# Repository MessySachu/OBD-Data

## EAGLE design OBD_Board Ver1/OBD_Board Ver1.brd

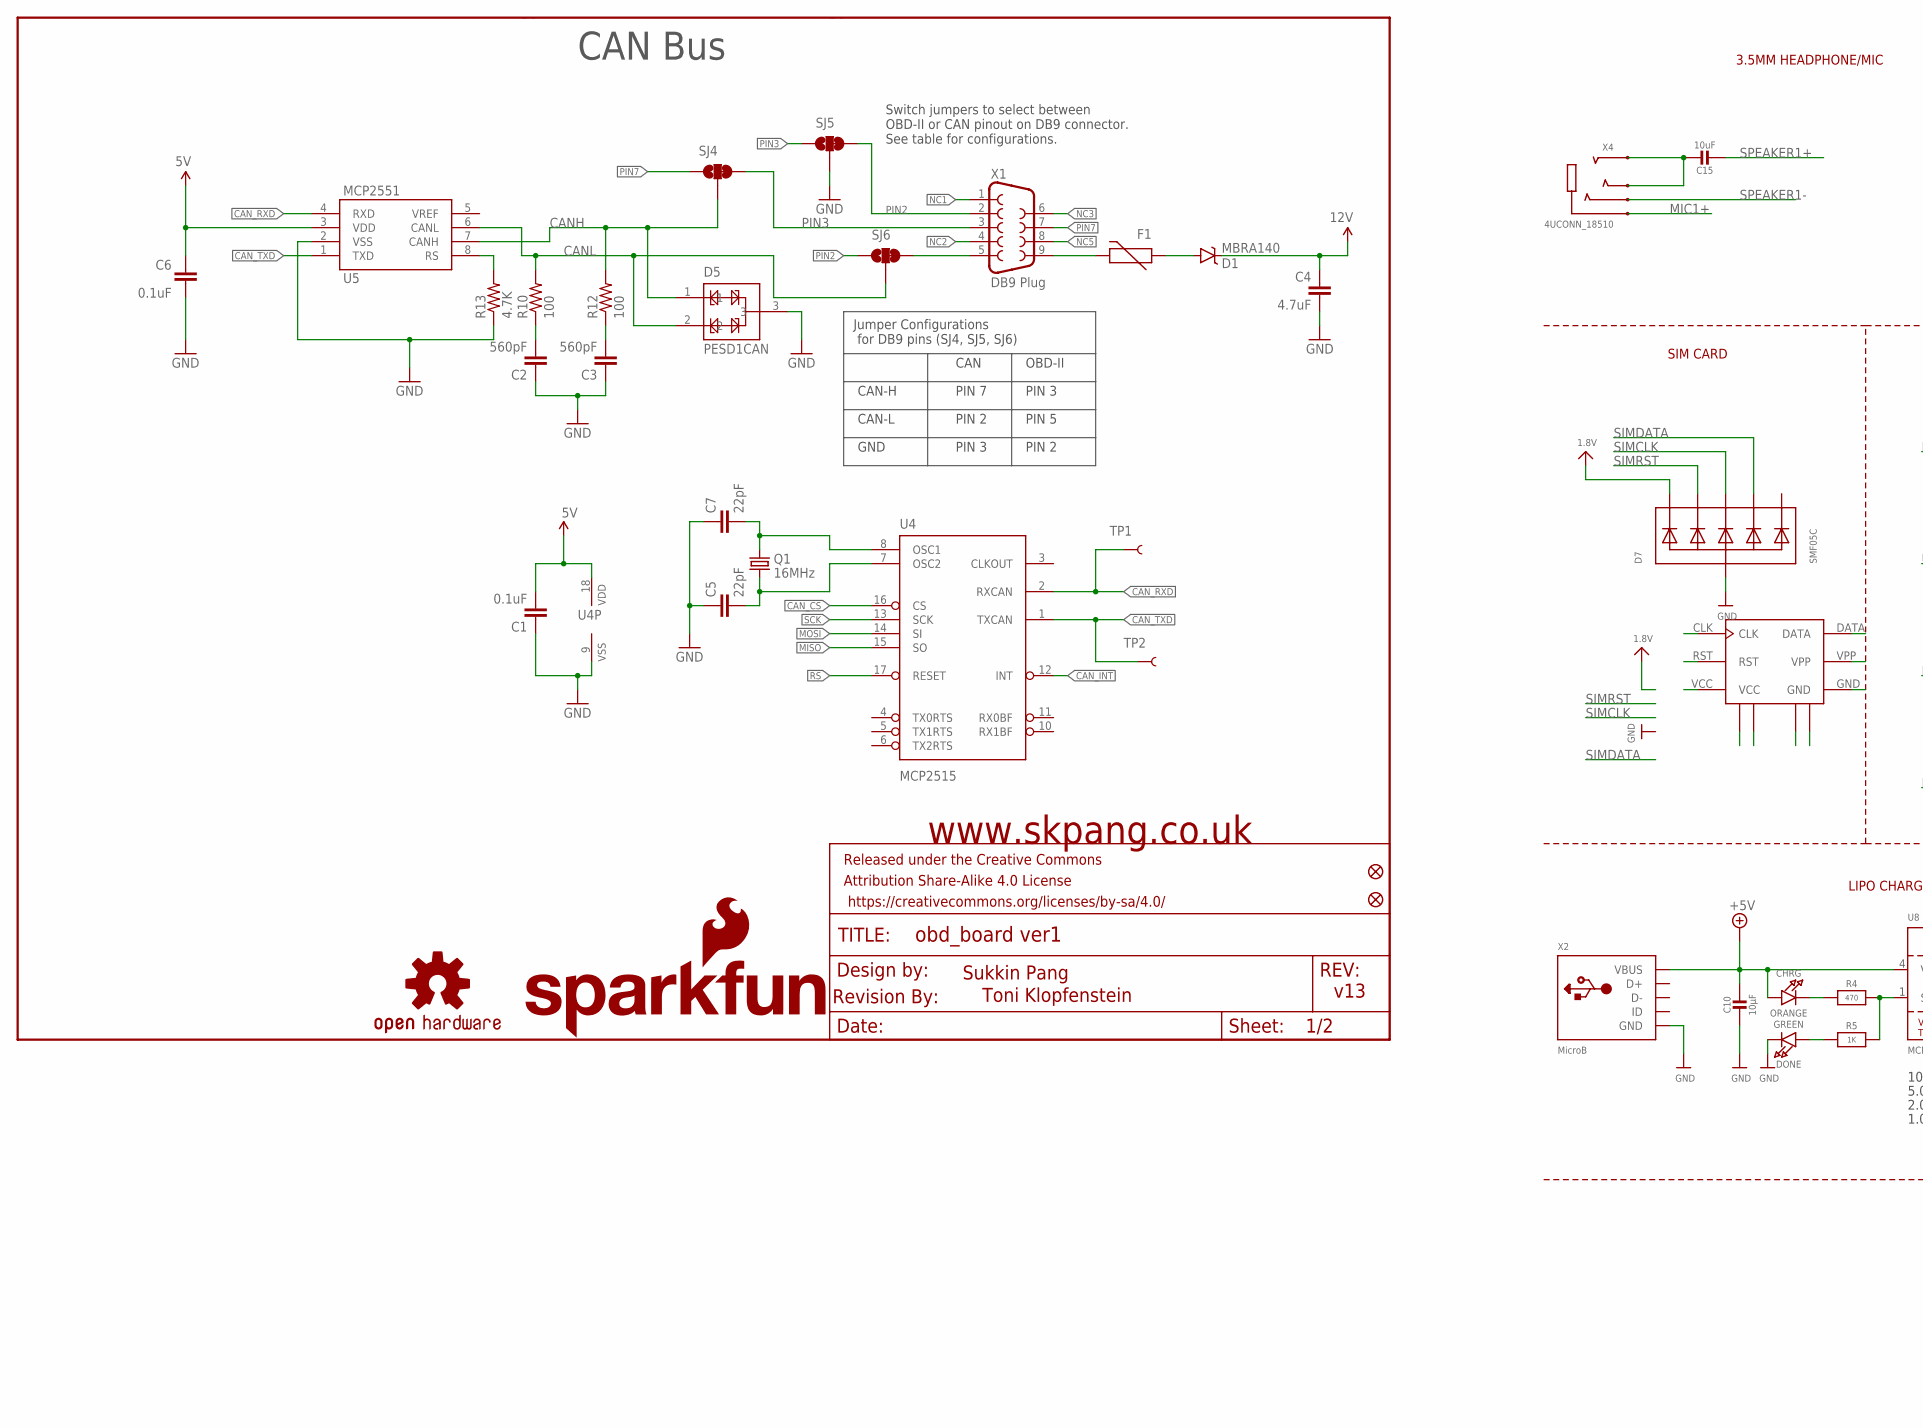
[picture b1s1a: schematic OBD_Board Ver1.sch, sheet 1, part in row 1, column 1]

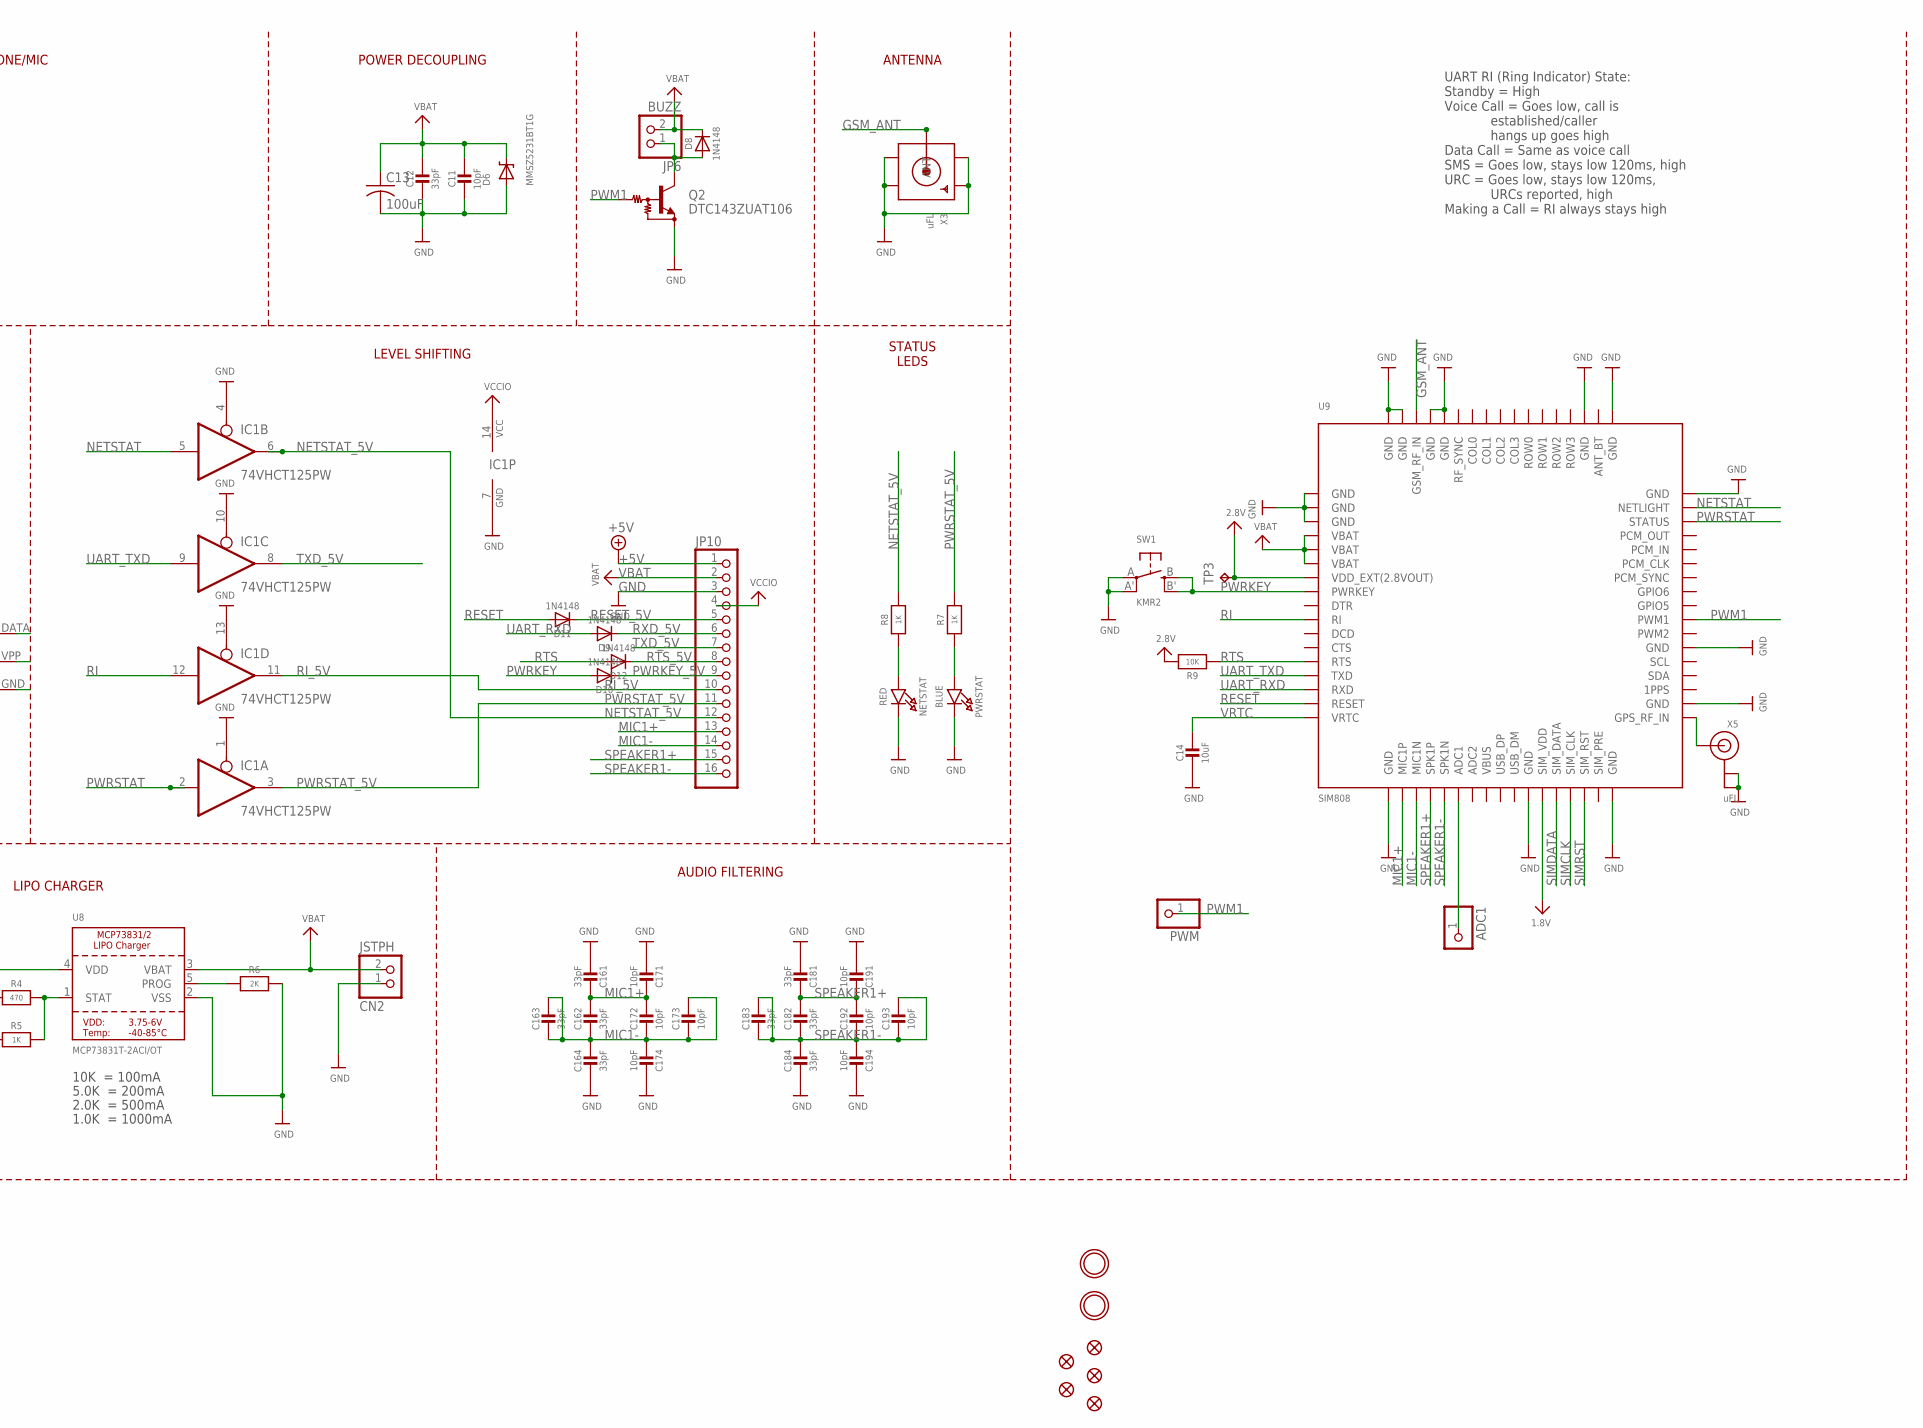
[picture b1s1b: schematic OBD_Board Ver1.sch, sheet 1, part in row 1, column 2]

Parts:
ADC1: PINHD-1X1CB; 1X01-CLEANBIG
C1, C6: 0.1uF; 0603-CAP
C2, C3: 560pF; 0603-CAP
C4: 4.7uF; 0603-CAP
C5, C7: 22pF; 0603-CAP
C10: 10µF; 0805-NO
C11: 10pF; 0805-NO
C12: 33pF; 0805-NO
C13: 100uF; C1210
C14, C15: 10uF; 0805-NO
C16, C18: 33pF; RESPACK_4X0603
C17, C19: 10pF; RESPACK_4X0603
CHRG: ORANGE; CHIPLED_0805_NOOUTLINE
CN2: JSTPH; JSTPH2
D1: MBRA140; SMA-DIODE
D5: PESD1CAN; SOT23-3
D6: MMSZ5231BT1G; SOD-123
D7: SMF05C; SOT363
D8, D9, D10, D11, D12: 1N4148; SOD-323
DONE: GREEN; CHIPLED_0805_NOOUTLINE
F1: PTCTHERMISTOR1206; PTC-1206
FID1, FID2, FID3, FID4, FID5: FIDUCIAL""; FIDUCIAL_1MM
FRAME1: FRAME-LETTER; CREATIVE_COMMONS
IC1: 74VHCT125PW; TSSOP14
JP2, JP3: FIDUCIAL1X2; FIDUCIAL-1X2
JP4: SFE_LOGO_NAME_FLAME.1_INCH; SFE_LOGO_NAME_FLAME_.1
JP6: BUZZ; 1X02_ROUND
JP10: HEADER-1X16ROUND; 1X16_ROUND
LOGO1: OSHW-LOGOM; OSHW-LOGO-M
NETSTAT: RED; CHIPLED_0805_NOOUTLINE
PWM: PINHD-1X1CB; 1X01-CLEANBIG
PWRSTAT: BLUE; CHIPLED_0805_NOOUTLINE
Q1: 16MHz; CRYSTAL-SMD-5X3
Q2: DTC143ZUAT106; SC59-BEC
R4: 470; 0805-NO
R5, R7, R8: 1K; 0805-NO
R6: 2K; 0805-NO
R9: 10K; 0805-NO
R10, R12: 100; 0603-RES
R13: 4.7K; 0603-RES
SJ4, SJ5, SJ6: JUMPER-PAD-3-2OF3_NC_BY_TRACE_SMALL; PAD-JUMPER-3-2OF3_NC_BY_TRACE_YES_SILK_FULL_BOX
SW1: KMR2; BTN_KMR2_4.6X2.8
TP1, TP2: TEST-POINT3X5; PAD.03X.05
TP3: TPTP11R; TP11R
U4: MCP2515; SO-18W
U5: MCP2551; SO08
U8: MCP73831T-2ACI/OT; SOT23-5
U9: SIM808; SIM900_SMT
U$1: REVISION
U$25: SCU-W0822XR-06
U$33, U$34: MOUNTINGHOLE2.5; MOUNTINGHOLE_2.5_PLATED
X1: DB9 Plug; DB9_MALE
X2: MicroB; 4UCONN_20329
X3: uFL; SMA_EDGELAUNCH_UFL
X4: 4UCONN_18510
X5: uFL; U.FL

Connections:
1.8V: D7.1 (C1), U9.P$29 (SIM_VDD), U$25.VCC
2.8V: R9.2, TP3.TP, U9.P$7 (VDD_EXT(2.8VOUT))
5V: C1.2, C6.2, U4.18 (VDD), U5.3 (VDD); also elsewhere on the board
12V: C4.1, D1.C; also elsewhere on the board
+5V: C10.1, CHRG.A, JP10.1, U8.4 (VDD), X2.VBUS
CANH: D5.1, R12.2, SJ4.2, U5.7 (CANH)
CANL: D5.2, R10.2, SJ6.2, U5.6 (CANL)
CAN_CS: U4.16 (CS); also elsewhere on the board
CAN_INT: U4.12 (INT); also elsewhere on the board
CAN_RXD: TP1.P$1, U4.2 (RXCAN), U5.4 (RXD)
CAN_TXD: TP2.P$1, U4.1 (TXCAN), U5.1 (TXD)
GND: C1.1, C2.1, C3.1, C4.2, C5.1, C6.1, C7.1, C10.2, C11.2, C12.2, C13.2, C14.2, C16.5 (2), C16.8 (2), C17.4 (1), C17.8 (2), C18.5 (2), C18.8 (2), C19.4 (1), C19.8 (2), CN2.1, D5.3, D6.A, D7.2 (A), DONE.C, IC1.1 (OE), IC1.4 (OE), IC1.7 (GND), IC1.10 (OE), IC1.13 (OE), JP10.3, NETSTAT.C, PWRSTAT.C, Q2.E, R6.2, R13.1, SJ5.2, SW1.A, SW1.A' (P1), U4.9 (VSS), U5.2 (VSS), U8.2 (VSS), U9.P$1 (GND), U9.P$2 (GND), U9.P$3 (GND), U9.P$18 (GND), U9.P$28 (GND), U9.P$34 (GND), U9.P$36 (GND), U9.P$40 (GND), U9.P$51 (GND), U9.P$52 (GND), U9.P$54 (GND), U9.P$64 (GND), U9.P$65 (GND), U9.P$67 (GND), U9.P$68 (GND), U$25.GND, U$25.GND_1 (GND1), U$25.GND_2 (GND2), U$25.GND_3 (GND3), U$25.GND_4 (GND4), X2.BASE@1 (GND), X2.BASE@2 (GND), X2.GND, X2.SPRT@1 (GND), X2.SPRT@2 (GND), X2.SPRT@3 (GND), X2.SPRT@4 (GND), X3.GND@1 (GND1), X3.GND@2 (GND2), X3.GND@3 (GND3), X3.GND@4 (GND4), X5.1 (GND), X5.2 (GND); also elsewhere on the board
GSM_ANT: U9.P$66 (GSM_RF_IN), X3.P (ANT)
HP+: C15.1, X4.2-TIP (RING3), X4.3-OUTER_SLEEVE (RING2)
MIC1+: C16.1, C16.2 (1), C17.1, C17.2 (1), JP10.13, U9.P$19 (MIC1P), X4.1-GND (TIP)
MIC1-: C16.3 (1), C16.4 (1), C16.6 (2), C16.7 (2), C17.3 (1), C17.5 (2), C17.6 (2), C17.7 (2), JP10.14, U9.P$20 (MIC1N)
MISO: U4.15 (SO); also elsewhere on the board
MOSI: U4.14 (SI); also elsewhere on the board
unnamed: SJ6.3, X1.5
unnamed: CHRG.C, R4.1
unnamed: R4.2, R5.2, U8.1 (STAT)
unnamed: R6.1, U8.5 (PROG)
unnamed: C2.2, R10.1
unnamed: C3.2, R12.1
unnamed: DONE.A, R5.1
unnamed: PWRSTAT.A, R7.1
unnamed: F1.2, X1.9
unnamed: R13.2, U5.8 (RS)
unnamed: D1.A, F1.1
unnamed: C7.2, Q1.3 (2), U4.8 (OSC1)
unnamed: C5.2, Q1.1, U4.7 (OSC2)
unnamed: NETSTAT.A, R8.1
unnamed: D8.A, JP6.1, Q2.C
unnamed: U9.P$35 (GPS_RF_IN), X5.3 (SIGNAL)
unnamed: ADC1.1, U9.P$23 (ADC1)
NC1: X1.1
NC2: X1.4
NC3: X1.6
NC5: X1.8
NETSTAT: IC1.5 (I), U9.P$50 (NETLIGHT)
NETSTAT_5V: IC1.6 (O), JP10.12, R8.2
PIN2: SJ5.3, SJ6.1, X1.2
PIN3: SJ4.3, SJ5.1, X1.3
PIN7: SJ4.1, X1.7
PWM1: PWM.1, Q2.B, U9.P$42 (PWM1)
PWRKEY: D10.A, SW1.B (S), SW1.B' (S1), U9.P$8 (PWRKEY)
PWRKEY_5V: D10.C, JP10.9
PWRSTAT: IC1.2 (I), U9.P$49 (STATUS)
PWRSTAT_5V: IC1.3 (O), JP10.11, R7.2
RESET: D11.A, U9.P$16 (RESET)
RESET_5V: D11.C, JP10.5
RI: IC1.12 (I), U9.P$10 (RI)
RI_5V: IC1.11 (O), JP10.10
RS: U4.17 (RESET); also elsewhere on the board
RTS: D12.A, R9.1, U9.P$13 (RTS)
RTS_5V: D12.C, JP10.8
RXD_5V: D9.C, JP10.6
SCK: U4.13 (SCK); also elsewhere on the board
SIMCLK: D7.4 (C3), U9.P$31 (SIM_CLK), U$25.CLK
SIMDATA: D7.5 (C4), U9.P$30 (SIM_DATA), U$25.DATA
SIMRST: D7.3 (C2), U9.P$32 (SIM_RST), U$25.RST
SPEAKER1+: C15.2, C18.1, C18.2 (1), C19.1, C19.2 (1), JP10.15, U9.P$21 (SPK1P)
SPEAKER1-: C18.3 (1), C18.4 (1), C18.6 (2), C18.7 (2), C19.3 (1), C19.5 (2), C19.6 (2), C19.7 (2), JP10.16, U9.P$22 (SPK1N), X4.4-INNER_SLEEVE (RING1)
TXD_5V: IC1.8 (O), JP10.7
UART_RXD: D9.A, U9.P$15 (RXD)
UART_TXD: IC1.9 (I), U9.P$14 (TXD)
VBAT: C11.1, C12.1, C13.1, CN2.2, D6.C, D8.C, JP6.2, JP10.2, U8.3 (VBAT), U9.P$4 (VBAT), U9.P$5 (VBAT), U9.P$6 (VBAT)
VBUS: U9.P$25 (VBUS)
VCCIO: IC1.14 (VCC), JP10.4
VRTC: C14.1, U9.P$17 (VRTC)

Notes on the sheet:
www.skpang.co.uk
Toni Klopfenstein
CAN Bus
CAN
OBD-II
CAN-H
CAN-L
GND
PIN 5
PIN 2
PIN 3
PIN 7
Jumper Configurations for DB9 pins (SJ4, SJ5, SJ6)
Switch jumpers to select between OBD-II or CAN pinout on DB9 connector. See table for configurations.
v13
Sukkin Pang
10K = 100mA
5.0K = 200mA
2.0K = 500mA
1.0K = 1000mA
UART RI (Ring Indicator) State: Standby = High Voice Call = Goes low, call is established/caller hangs up goes high Data Call = Same as voice call SMS = Goes low, stays low 120ms, high URC = Goes low, stays low 120ms, URCs reported, high Making a Call = RI always stays high
ANTENNA
POWER DECOUPLING
3.5MM HEADPHONE/MIC
SIM CARD
LEVEL SHIFTING
LIPO CHARGER
AUDIO FILTERING
STATUS LEDS

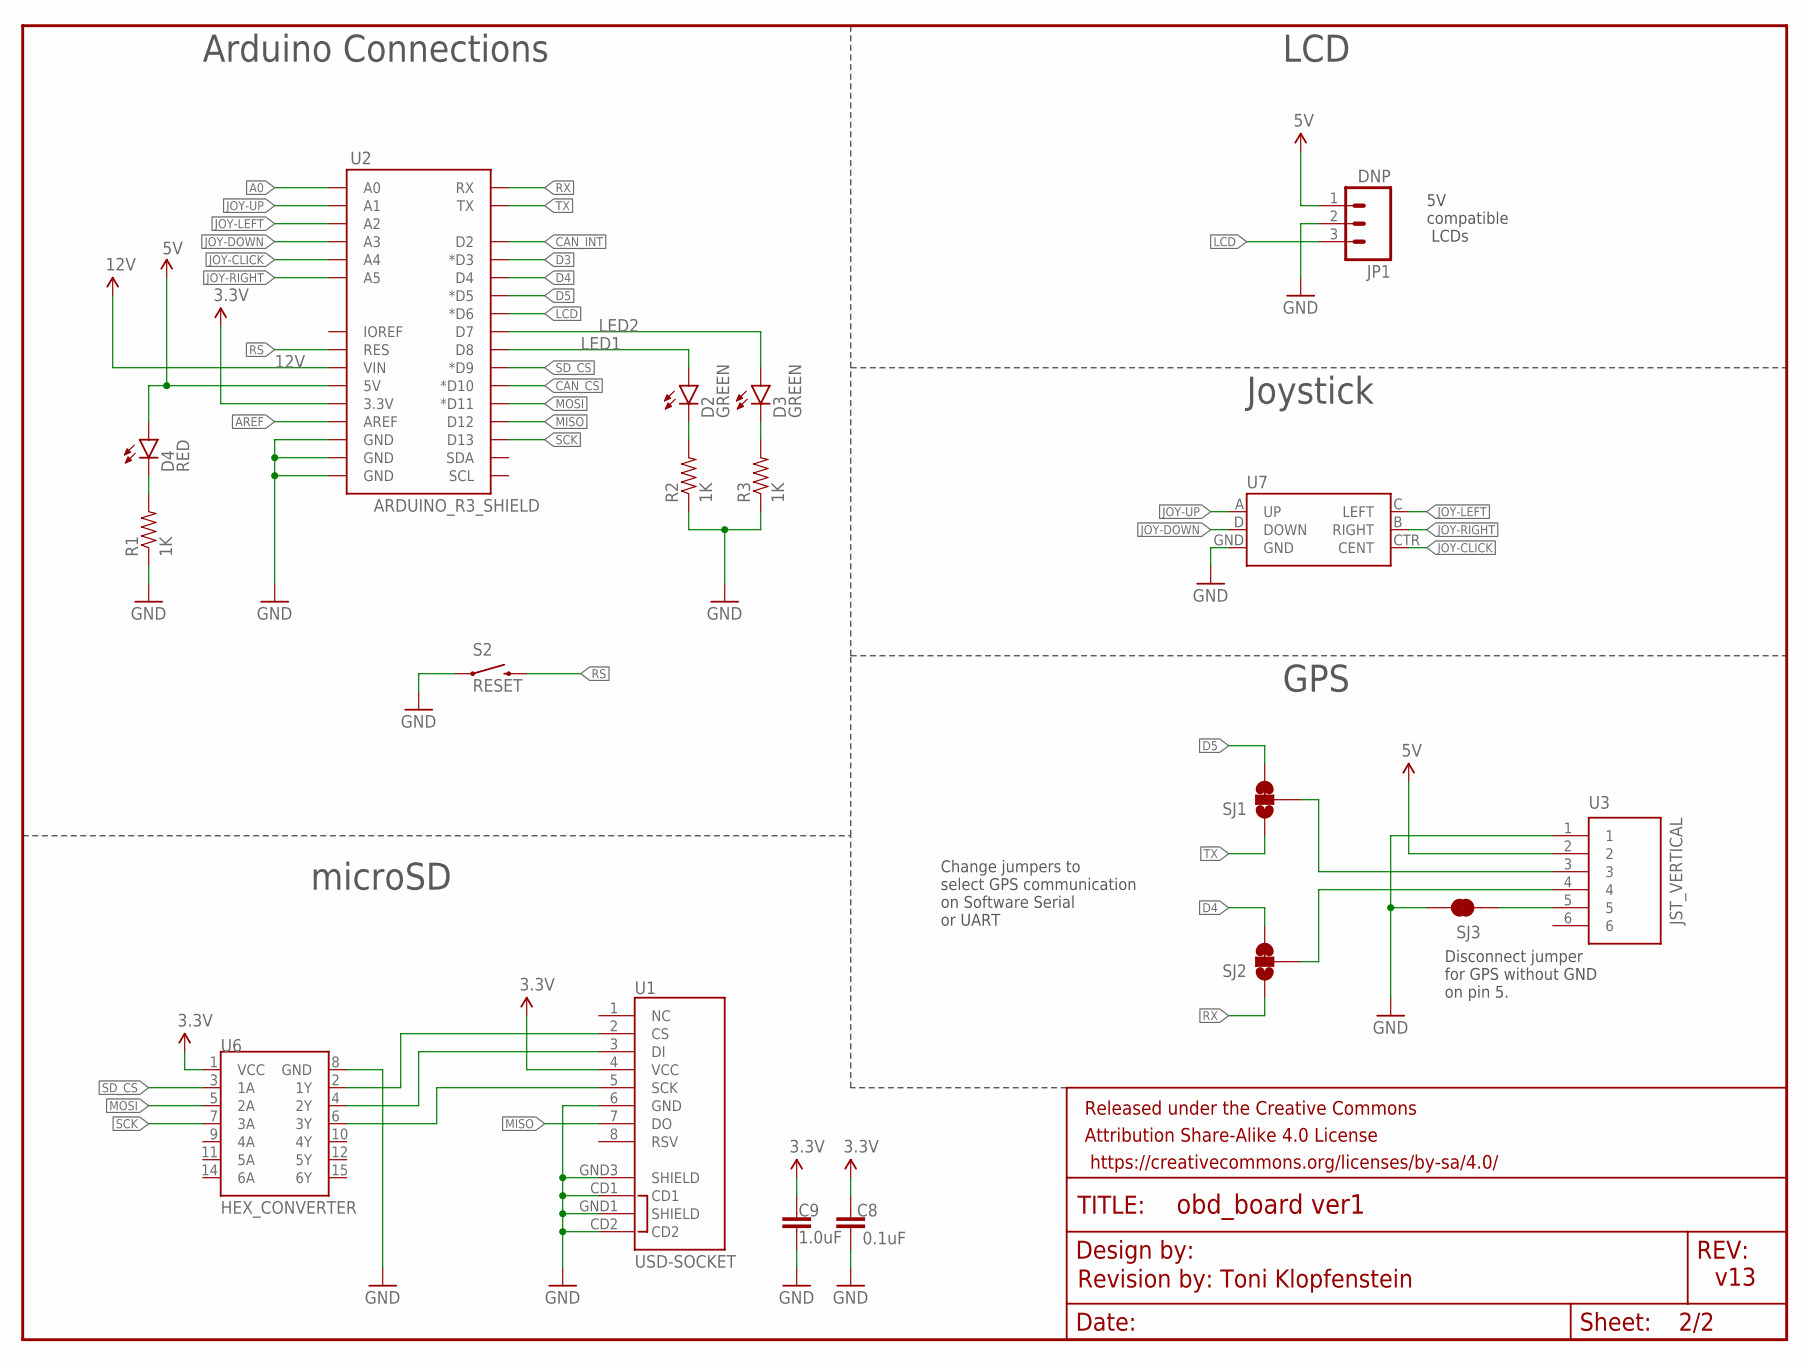
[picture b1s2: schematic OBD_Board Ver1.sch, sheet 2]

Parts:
C8: 0.1uF; 0603-CAP
C9: 1.0uF; 0603-CAP
D2, D3: GREEN; LED-0603
D4: RED; LED-0603
FRAME2: FRAME-LETTERNO_PACKAGE; DUMMY
JP1: DNP; MOLEX-1X3_LOCK
R1, R2, R3: 1K; 0603-RES
S2: RESET; TACTILE-SWITCH-SMD
SJ1, SJ2: JUMPER-PAD-3-2OF3_NC_BY_TRACE_SMALL; PAD-JUMPER-3-2OF3_NC_BY_TRACE_YES_SILK_FULL_BOX
SJ3: JUMPER-PAD-2-NC_BY_TRACE; PAD-JUMPER-2-NC_BY_TRACE_YES_SILK
U1: USD-SOCKET; MICROSD_1:1
U2: ARDUINO_R3_SHIELD; UNO_R3_SHIELD
U3: JST_VERTICAL; JST-6-SMD-VERT-1.0MM
U6: HEX_CONVERTER; SO016
U7: JOYSTICK_MINI

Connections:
3.3V: C8.2, C9.1, U1.4 (VCC), U2.3.3V, U6.1 (VCC)
5V: D4.A, JP1.1, U2.5V, U3.2; also elsewhere on the board
12V: U2.VIN; also elsewhere on the board
A0: U2.A0
AREF: U2.AREF
CAN_CS: U2.D10 (*D10); also elsewhere on the board
CAN_INT: U2.D2; also elsewhere on the board
D3: U2.D3 (*D3)
D4: SJ2.3, U2.D4
D5: SJ1.3, U2.D5 (*D5)
GND: C8.1, C9.2, JP1.2, R1.1, R2.1, R3.1, S2.1, SJ3.2, U1.6 (GND), U1.CD1, U1.CD2, U1.GND1 (SHIELD), U1.GND3 (SHIELD), U2.GND@0 (GND), U2.GND@1 (GND), U2.GND@2 (GND), U3.1, U6.8 (GND), U7.GND; also elsewhere on the board
JOY-CLICK: U2.A4, U7.CTR (CENT)
JOY-DOWN: U2.A3, U7.D (DOWN)
JOY-LEFT: U2.A2, U7.C (LEFT)
JOY-RIGHT: U2.A5, U7.B (RIGHT)
JOY-UP: U2.A1, U7.A (UP)
LCD: JP1.3, U2.D6 (*D6)
LED1: D2.A, U2.D8
LED2: D3.A, U2.D7
MISO: U1.7 (DO), U2.D12; also elsewhere on the board
MOSI: U2.D11 (*D11), U6.5 (2A); also elsewhere on the board
unnamed: SJ3.1, U3.5
unnamed: D4.C, R1.2
unnamed: D2.C, R2.2
unnamed: D3.C, R3.2
unnamed: U1.2 (CS), U6.2 (1Y)
unnamed: U1.3 (DI), U6.4 (2Y)
unnamed: SJ1.2, U3.3
unnamed: SJ2.2, U3.4
unnamed: U1.5 (SCK), U6.6 (3Y)
RS: S2.3 (2), U2.RES; also elsewhere on the board
RX: SJ2.1, U2.RX
SCK: U2.D13, U6.7 (3A); also elsewhere on the board
SD_CS: U2.D9 (*D9), U6.3 (1A)
TX: SJ1.1, U2.TX

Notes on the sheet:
Arduino Connections
LCD
Joystick
5V compatible LCDs
GPS
Change jumpers to select GPS communication on Software Serial or UART
Disconnect jumper for GPS without GND on pin 5.
microSD
Revision by: Toni Klopfenstein
v13

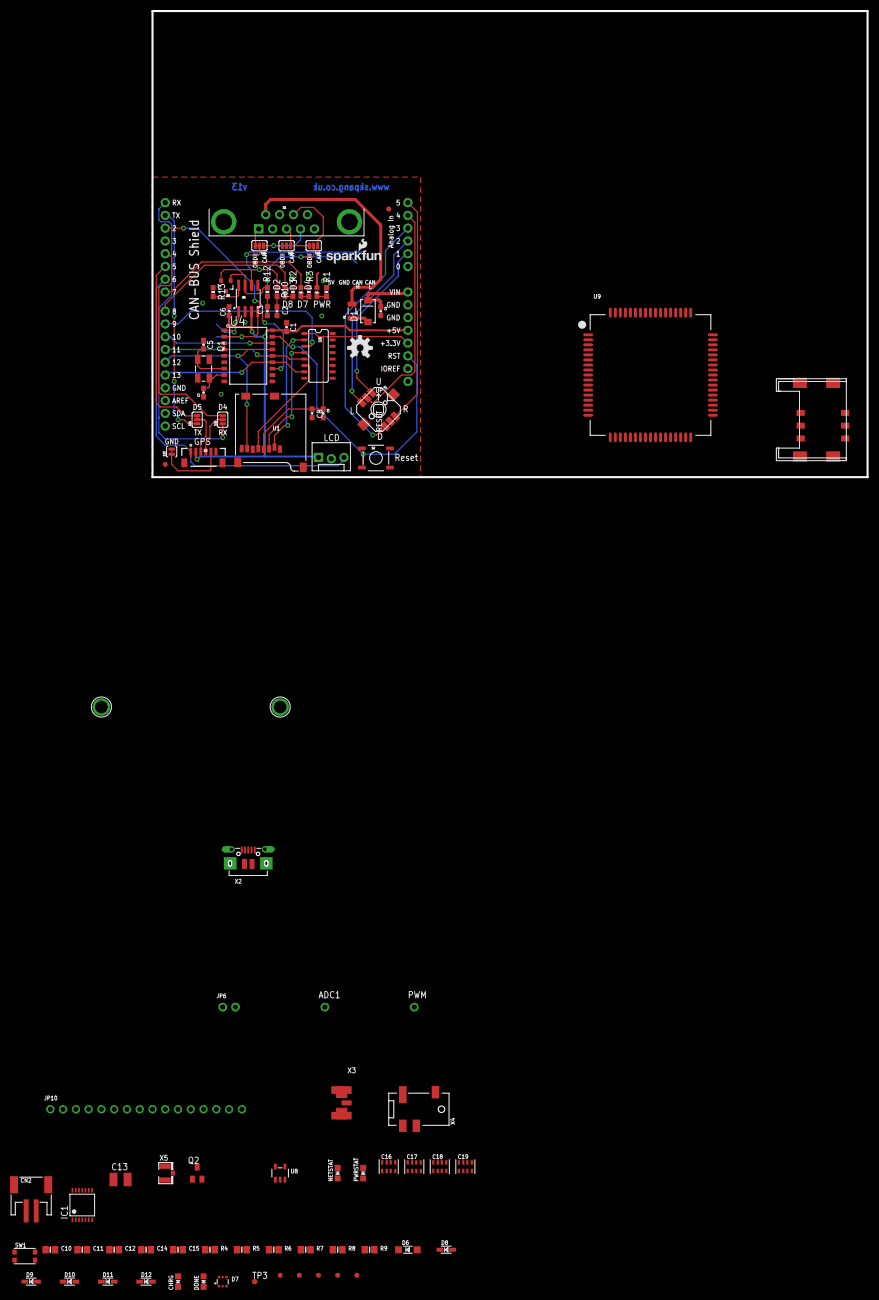
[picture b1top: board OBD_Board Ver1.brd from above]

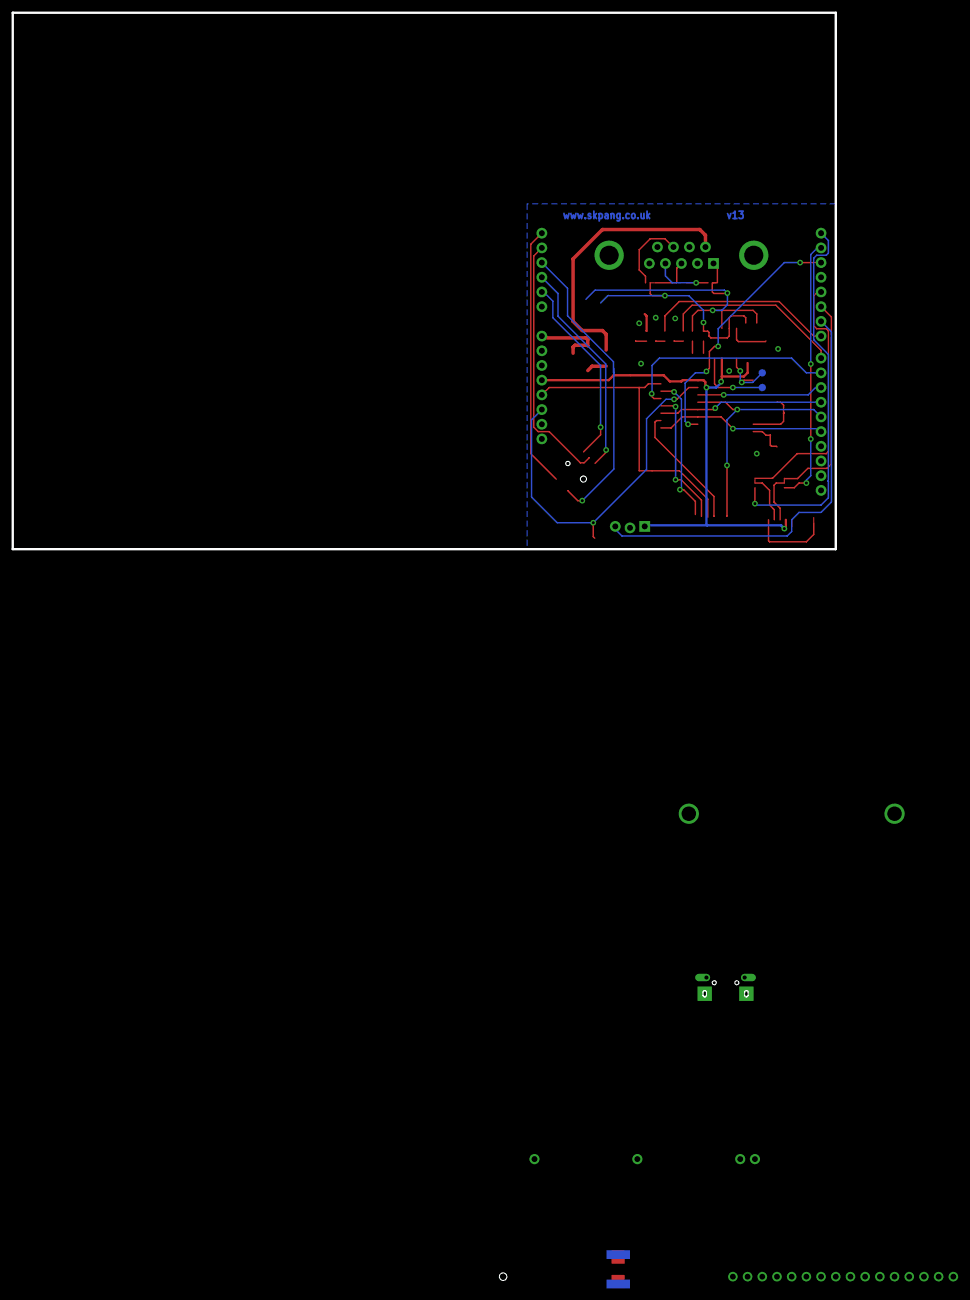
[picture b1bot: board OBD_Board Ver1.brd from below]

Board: 2 copper layers, 97 parts (2 on the bottom side), 88 nets.

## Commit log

2017-07-16 Initial push
2017-07-17 Added Boolean to check if Data is posted
2017-07-17 Tested GSM code. Initial push

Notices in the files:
parts and their libraries:
SparkFun-Boards: Licensing: CC v3.0 Share-Alike You are welcome to use this library for commercial purposes.
SparkFun-Aesthetics: Released under the Creative Commons Attribution Share-Alike 4.0 License
SparkFun-Aesthetics: https://creativecommons.org/licenses/by-sa/4.0
